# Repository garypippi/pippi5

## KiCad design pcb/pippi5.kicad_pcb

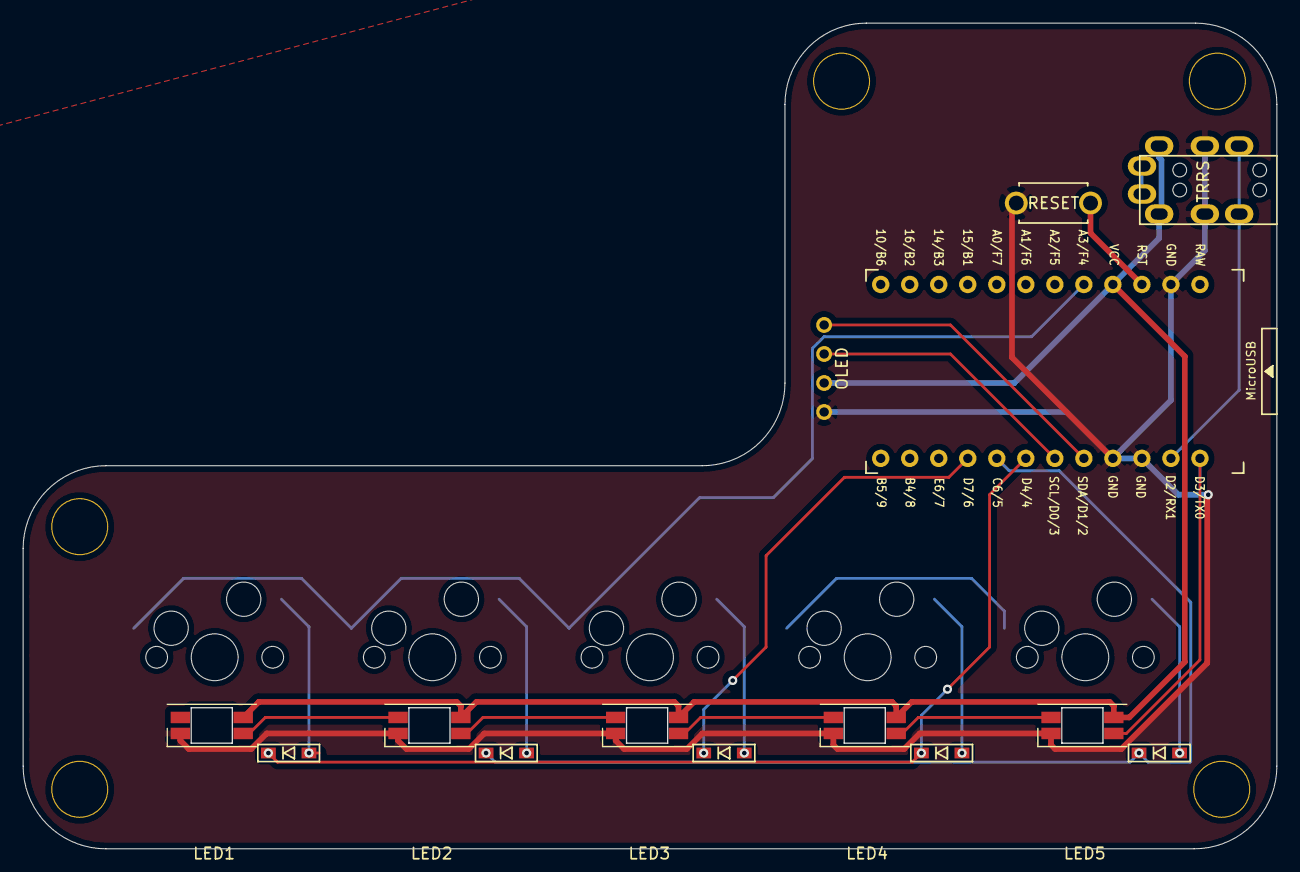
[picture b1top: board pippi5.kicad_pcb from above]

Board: 2 copper layers, 109.7 x 72.2 mm, 24 parts (0 on the bottom side), 21 nets.

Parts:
D1, D2, D3, D4, D5: D; D3_SMD
J1: MJ-4PP-9
LED1, LED2, LED3, LED4, LED5: YS-SK6812MINI-E
OL1: OLED; OLED_v2
Ref**: Val**; HOLE
Ref**#2, Ref**#3, Ref**#4, Ref**#5: Val**; HOLE
SW1, SW2, SW3, SW4, SW5: SW_PUSH; CherryMX_Hotswap
SW6: SW_PUSH; ResetSW
U1: ProMicro; ProMicro_v3.5

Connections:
GND: J1.C, LED1.3, LED2.3, LED3.3, LED4.3, LED5.3, OL1.4, SW6.2, U1.3, U1.4, U1.23
unnamed: D1.2, SW1.2
unnamed: D2.2, SW2.2
unnamed: D3.2, SW3.2
unnamed: D4.2, SW4.2
unnamed: D5.2, SW5.2
unnamed: LED1.2, LED2.4
unnamed: LED2.2, LED3.4
unnamed: LED3.2, LED4.4
unnamed: LED4.2, LED5.4
VCC: J1.D, LED1.1, LED2.1, LED3.1, LED4.1, LED5.1, OL1.3, U1.21
col0: SW1.1, SW2.1, SW3.1, U1.20
col2: SW4.1, SW5.1
data: J1.B, U1.2
led: LED5.2, U1.1
reset: SW6.1, U1.22
row0: D1.1, D4.1, U1.7
row1: D2.1, D5.1, U1.8
row2: D3.1, U1.9
scl: OL1.2, U1.6
sda: OL1.1, U1.5

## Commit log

2021-09-16 (・_・)
2021-09-16 Add submodule
2021-09-24 v0.1
